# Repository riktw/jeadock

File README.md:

# jeadock
Dock for the Lichee RV to provide Ethernet, GPIO and more

More information on the related [blog post](https://justanotherelectronicsblog.com/?p=1107).

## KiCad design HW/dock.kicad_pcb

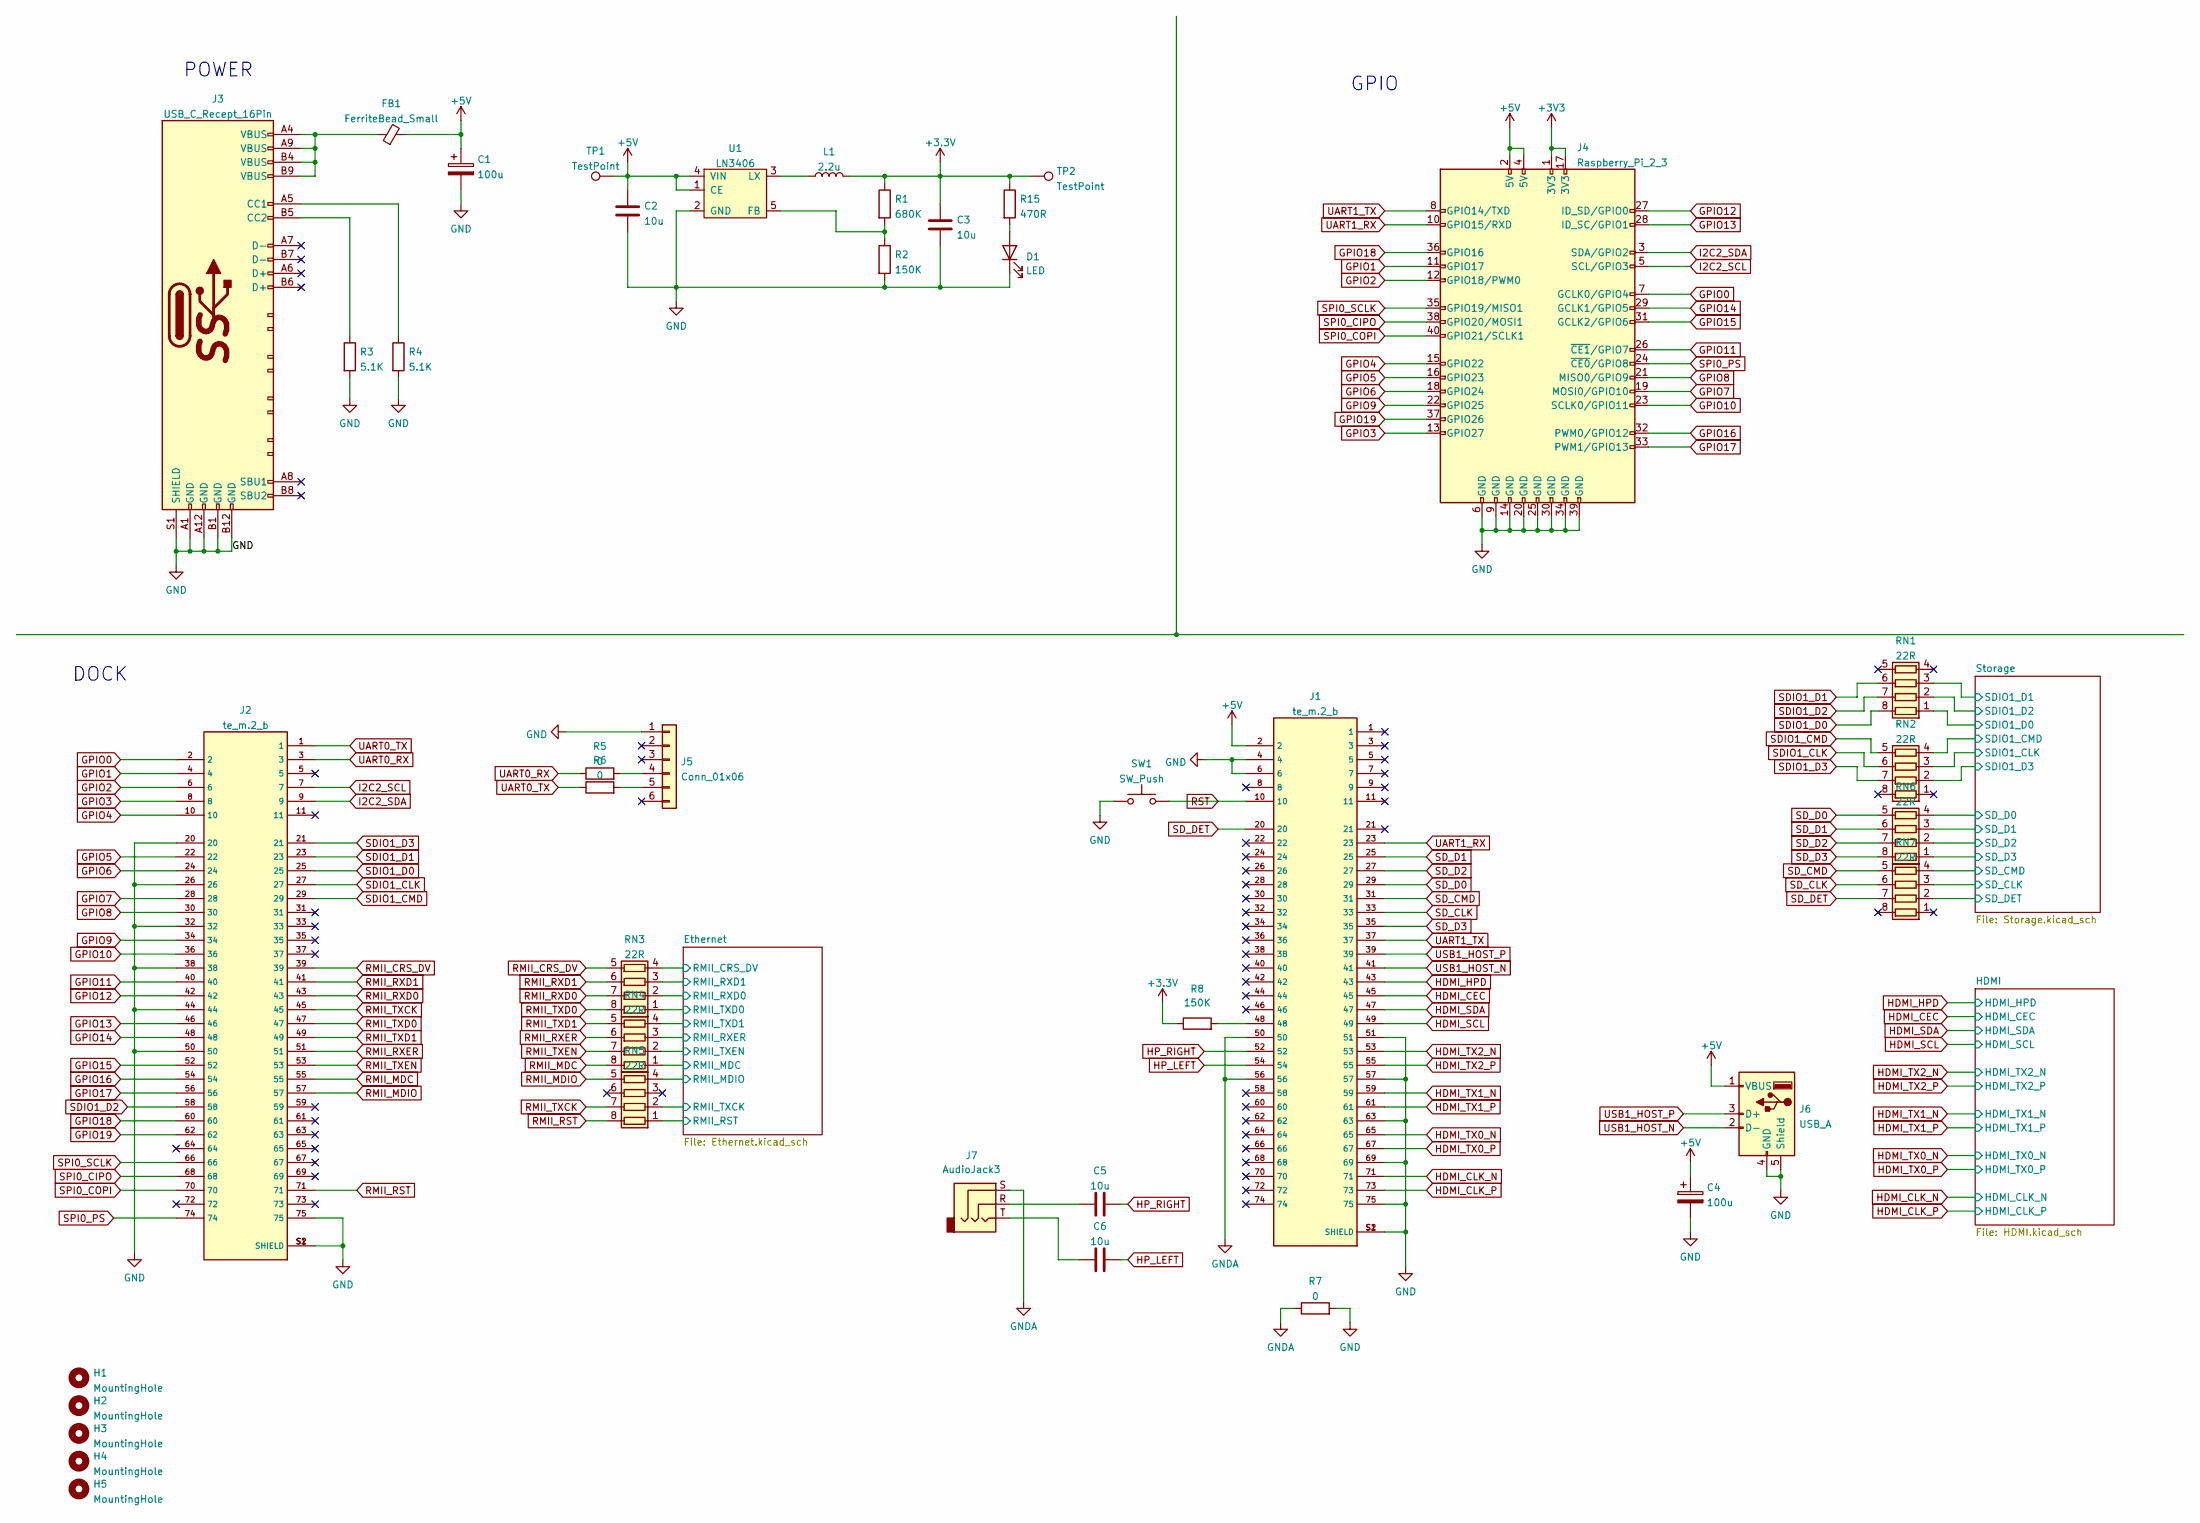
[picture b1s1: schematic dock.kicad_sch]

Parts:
C1, C4: 100u; CP_Elec_6.3x7.7
C2, C3, C5, C6: 10u; C_0603_1608Metric; JLC C96446
D1: LED; LED_0603_1608Metric; JLC C72043
FB1: FerriteBead_Small; L_0603_1608Metric
H1: MountingHole; MountingHole_2.2mm_M2
H2, H3, H4, H5: MountingHole; MountingHole_3.2mm_M3
J1, J2: te_m.2_b; TE_2199230-3; JLC C2761526
J3: USB_C_Recept_16Pin
J4: Raspberry_Pi_2_3; PinHeader_2x20_P2.54mm_Vertical
J5: Conn_01x06; PinHeader_1x06_P2.54mm_Vertical
J6: USB_A; USB_A_CONNFLY_DS1095-WNR0
J7: AudioJack3; audio_jack_3.5_C18167; JLC C18167
L1: 2.2u; L_0805_2012Metric_Pad1.15x1.40mm_HandSolder; Farnell 2776807
R1: 680K; R_0603_1608Metric; JLC C25822
R2, R8: 150K; R_0603_1608Metric; JLC C22807
R3, R4: 5.1K; R_0603_1608Metric; JLC C23186
R5, R6, R7: 0; R_0603_1608Metric
R15: 470R; R_0603_1608Metric
RN1, RN2, RN3, RN4, RN5, RN6, RN7: 22R; R_Array_Convex_4x0402; Farnell 3550014
SW1: SW_Push; SW_SPST_CK_RS282G05A3
TP1, TP2: TestPoint; TestPoint_Pad_1.5x1.5mm
U1: LN3406; SOT-23-5; JLC C190828

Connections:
+5V: C1.1, C2.1, C4.1, FB1.2, J1.2, J4.2 (5V), J4.4 (5V), J6.1 (VBUS), TP1.1, U1.1 (CE), U1.4 (VIN); also elsewhere on the board
/Ethernet/RMII_CRS_DV: RN3.4 (R4.1); also elsewhere on the board
/Ethernet/RMII_MDC: RN4.1 (R1.1); also elsewhere on the board
/Ethernet/RMII_MDIO: RN5.4 (R4.1); also elsewhere on the board
/Ethernet/RMII_RXD0: RN3.2 (R2.1); also elsewhere on the board
/Ethernet/RMII_RXD1: RN3.3 (R3.1); also elsewhere on the board
/Ethernet/RMII_RXER: RN4.3 (R3.1); also elsewhere on the board
/Ethernet/RMII_TXCK: RN5.2 (R2.1); also elsewhere on the board
/Ethernet/RMII_TXD0: RN3.1 (R1.1); also elsewhere on the board
/Ethernet/RMII_TXD1: RN4.4 (R4.1); also elsewhere on the board
/Ethernet/RMII_TXEN: RN4.2 (R2.1); also elsewhere on the board
/Storage/SDIO1_CLK: RN2.3 (R3.1); also elsewhere on the board
/Storage/SDIO1_CMD: RN2.4 (R4.1); also elsewhere on the board
/Storage/SDIO1_D0: RN1.1 (R1.1); also elsewhere on the board
/Storage/SDIO1_D1: RN1.3 (R3.1); also elsewhere on the board
/Storage/SDIO1_D2: RN1.2 (R2.1); also elsewhere on the board
/Storage/SDIO1_D3: RN2.2 (R2.1); also elsewhere on the board
/Storage/SD_CLK: RN7.3 (R3.1); also elsewhere on the board
/Storage/SD_CMD: RN7.4 (R4.1); also elsewhere on the board
/Storage/SD_D0: RN6.4 (R4.1); also elsewhere on the board
/Storage/SD_D1: RN6.3 (R3.1); also elsewhere on the board
/Storage/SD_D2: RN6.2 (R2.1); also elsewhere on the board
/Storage/SD_D3: RN6.1 (R1.1); also elsewhere on the board
/Storage/SD_DET: RN7.2 (R2.1); also elsewhere on the board
GND: C1.2, C2.2, C3.2, C4.2, D1.1 (K), J1.4, J1.6, J1.51, J1.57, J1.63, J1.69, J1.75, J1.S1 (SHIELD), J1.S2 (SHIELD), J2.20, J2.26, J2.32, J2.38, J2.44, J2.50, J2.75, J2.S1 (SHIELD), J2.S2 (SHIELD), J3.A1 (GND), J3.A12 (GND), J3.B1 (GND), J3.B12 (GND), J3.S1 (SHIELD), J4.6 (GND), J4.9 (GND), J4.14 (GND), J4.20 (GND), J4.25 (GND), J4.30 (GND), J4.34 (GND), J4.39 (GND), J5.1, J6.4 (GND), J6.5 (Shield), R2.2, R3.2, R4.2, R7.2, SW1.1, U1.2 (GND); also elsewhere on the board
GNDA: J1.50, J1.56, J7.S, R7.1
GPIO0: J2.2, J4.7 (GCLK0/GPIO4)
GPIO1: J2.4, J4.11 (GPIO17)
GPIO2: J2.6, J4.12 (GPIO18/PWM0)
GPIO3: J2.8, J4.13 (GPIO27)
GPIO4: J2.10, J4.15 (GPIO22)
GPIO5: J2.22, J4.16 (GPIO23)
GPIO6: J2.24, J4.18 (GPIO24)
GPIO7: J2.28, J4.19 (MOSI0/GPIO10)
GPIO8: J2.30, J4.21 (MISO0/GPIO9)
GPIO9: J2.34, J4.22 (GPIO25)
GPIO10: J2.36, J4.23 (SCLK0/GPIO11)
GPIO11: J2.40, J4.26 (~CE1/GPIO7)
GPIO12: J2.42, J4.27 (ID_SD/GPIO0)
GPIO13: J2.46, J4.28 (ID_SC/GPIO1)
GPIO14: J2.48, J4.29 (GCLK1/GPIO5)
GPIO15: J2.52, J4.31 (GCLK2/GPIO6)
GPIO16: J2.54, J4.32 (PWM0/GPIO12)
GPIO17: J2.56, J4.33 (PWM1/GPIO13)
GPIO18: J2.60, J4.36 (GPIO16)
GPIO19: J2.62, J4.37 (GPIO26)
HDMI_CEC: J1.45; also elsewhere on the board
HDMI_CLK_N: J1.71; also elsewhere on the board
HDMI_CLK_P: J1.73; also elsewhere on the board
HDMI_HPD: J1.43; also elsewhere on the board
HDMI_SCL: J1.49; also elsewhere on the board
HDMI_SDA: J1.47; also elsewhere on the board
HDMI_TX0_N: J1.65; also elsewhere on the board
HDMI_TX0_P: J1.67; also elsewhere on the board
HDMI_TX1_N: J1.59; also elsewhere on the board
HDMI_TX1_P: J1.61; also elsewhere on the board
HDMI_TX2_N: J1.53; also elsewhere on the board
HDMI_TX2_P: J1.55; also elsewhere on the board
HP_LEFT: C6.2, J1.54
HP_RIGHT: C5.2, J1.52
I2C2_SCL: J2.7, J4.5 (SCL/GPIO3)
I2C2_SDA: J2.9, J4.3 (SDA/GPIO2)
unnamed: C5.1, J7.R
unnamed: C6.1, J7.T
unnamed: D1.2 (A), R15.2
unnamed: FB1.1, J3.A4 (VBUS), J3.A9 (VBUS), J3.B4 (VBUS), J3.B9 (VBUS)
unnamed: J1.48, R8.2
unnamed: J3.A5 (CC1), R4.1
unnamed: J3.B5 (CC2), R3.1
unnamed: J5.4, R5.2
unnamed: J5.5, R6.2
unnamed: L1.1, U1.3 (LX)
unnamed: R1.2, R2.1, U1.5 (FB)
RMII_CRS_DV: J2.39, RN3.5 (R4.2)
RMII_MDC: J2.55, RN4.8 (R1.2)
RMII_MDIO: J2.57, RN5.5 (R4.2)
RMII_RST: J2.71, RN5.8 (R1.2)
RMII_RXD0: J2.43, RN3.7 (R2.2)
RMII_RXD1: J2.41, RN3.6 (R3.2)
RMII_RXER: J2.51, RN4.6 (R3.2)
RMII_TXCK: J2.45, RN5.7 (R2.2)
RMII_TXD0: J2.47, RN3.8 (R1.2)
RMII_TXD1: J2.49, RN4.5 (R4.2)
RMII_TXEN: J2.53, RN4.7 (R2.2)
RST: J1.10, SW1.2
RST_PHY: RN5.1 (R1.1); also elsewhere on the board
SDIO1_CLK: J2.27, RN2.6 (R3.2)
SDIO1_CMD: J2.29, RN2.5 (R4.2)
SDIO1_D0: J2.25, RN1.8 (R1.2)
SDIO1_D1: J2.23, RN1.6 (R3.2)
SDIO1_D2: J2.58, RN1.7 (R2.2)
SDIO1_D3: J2.21, RN2.7 (R2.2)
SD_CLK: J1.33, RN7.6 (R3.2)
SD_CMD: J1.31, RN7.5 (R4.2)
SD_D0: J1.29, RN6.5 (R4.2)
SD_D1: J1.25, RN6.6 (R3.2)
SD_D2: J1.27, RN6.7 (R2.2)
SD_D3: J1.35, RN6.8 (R1.2)
SD_DET: J1.20, RN7.7 (R2.2)
SPI0_CIPO: J2.68, J4.38 (GPIO20/MOSI1)
SPI0_COPI: J2.70, J4.40 (GPIO21/SCLK1)
SPI0_PS: J2.74, J4.24 (~CE0/GPIO8)
SPI0_SCLK: J2.66, J4.35 (GPIO19/MISO1)
UART0_RX: J2.3, R5.1
UART0_TX: J2.1, R6.1
UART1_RX: J1.23, J4.10 (GPIO15/RXD)
UART1_TX: J1.37, J4.8 (GPIO14/TXD)
USB1_HOST_N: J1.41, J6.2 (D-)
USB1_HOST_P: J1.39, J6.3 (D+)

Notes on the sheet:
GPIO
POWER
DOCK

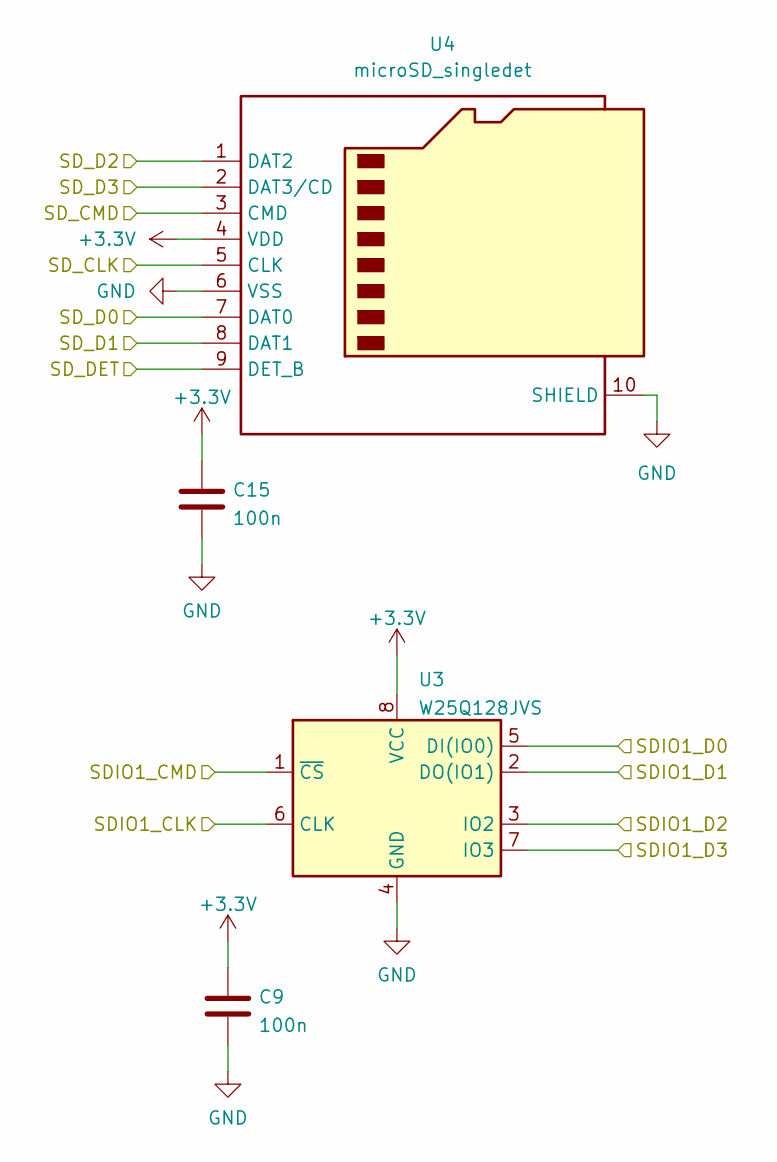
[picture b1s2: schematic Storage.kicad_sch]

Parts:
C9, C15: 100n; C_0603_1608Metric; JLC C14663
U3: W25Q128JVS; SOIC-8_5.23x5.23mm_P1.27mm; JLC C97521
U4: microSD_singledet; microSD Hanbo Electronic TF-018; JLC C961679

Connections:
/Storage/SDIO1_CLK: U3.6 (CLK); also elsewhere on the board
/Storage/SDIO1_CMD: U3.1 (~CS); also elsewhere on the board
/Storage/SDIO1_D0: U3.5 (DI(IO0)); also elsewhere on the board
/Storage/SDIO1_D1: U3.2 (DO(IO1)); also elsewhere on the board
/Storage/SDIO1_D2: U3.3 (IO2); also elsewhere on the board
/Storage/SDIO1_D3: U3.7 (IO3); also elsewhere on the board
/Storage/SD_CLK: U4.5 (CLK); also elsewhere on the board
/Storage/SD_CMD: U4.3 (CMD); also elsewhere on the board
/Storage/SD_D0: U4.7 (DAT0); also elsewhere on the board
/Storage/SD_D1: U4.8 (DAT1); also elsewhere on the board
/Storage/SD_D2: U4.1 (DAT2); also elsewhere on the board
/Storage/SD_D3: U4.2 (DAT3/CD); also elsewhere on the board
/Storage/SD_DET: U4.9 (DET_B); also elsewhere on the board
GND: C9.2, C15.2, U3.4 (GND), U4.6 (VSS), U4.10 (SHIELD); also elsewhere on the board

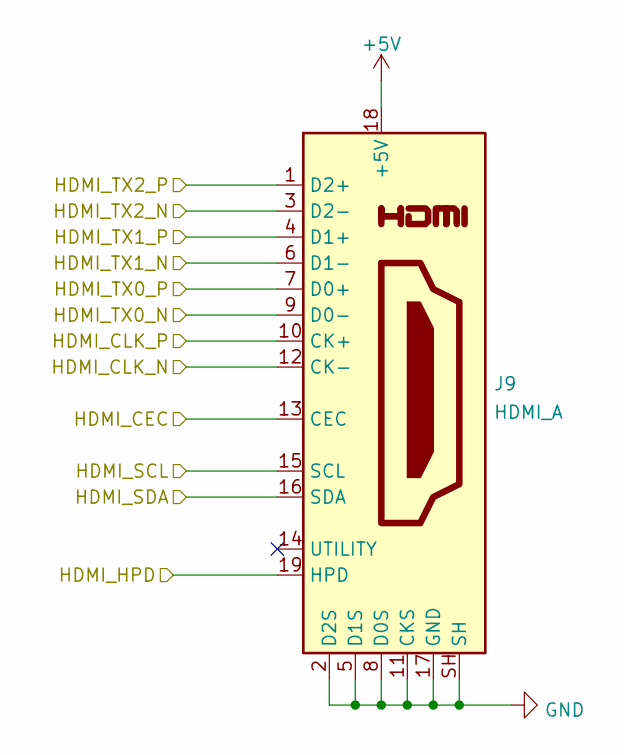
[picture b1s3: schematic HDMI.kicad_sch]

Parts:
J9: HDMI_A; HDMI_A_XUNPU_HDMI-001S; JLC C720616

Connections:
+5V: J9.18 (+5V); also elsewhere on the board
GND: J9.2 (D2S), J9.5 (D1S), J9.8 (D0S), J9.11 (CKS), J9.17 (GND), J9.SH; also elsewhere on the board
HDMI_CEC: J9.13 (CEC); also elsewhere on the board
HDMI_CLK_N: J9.12 (CK-); also elsewhere on the board
HDMI_CLK_P: J9.10 (CK+); also elsewhere on the board
HDMI_HPD: J9.19 (HPD); also elsewhere on the board
HDMI_SCL: J9.15 (SCL); also elsewhere on the board
HDMI_SDA: J9.16 (SDA); also elsewhere on the board
HDMI_TX0_N: J9.9 (D0-); also elsewhere on the board
HDMI_TX0_P: J9.7 (D0+); also elsewhere on the board
HDMI_TX1_N: J9.6 (D1-); also elsewhere on the board
HDMI_TX1_P: J9.4 (D1+); also elsewhere on the board
HDMI_TX2_N: J9.3 (D2-); also elsewhere on the board
HDMI_TX2_P: J9.1 (D2+); also elsewhere on the board

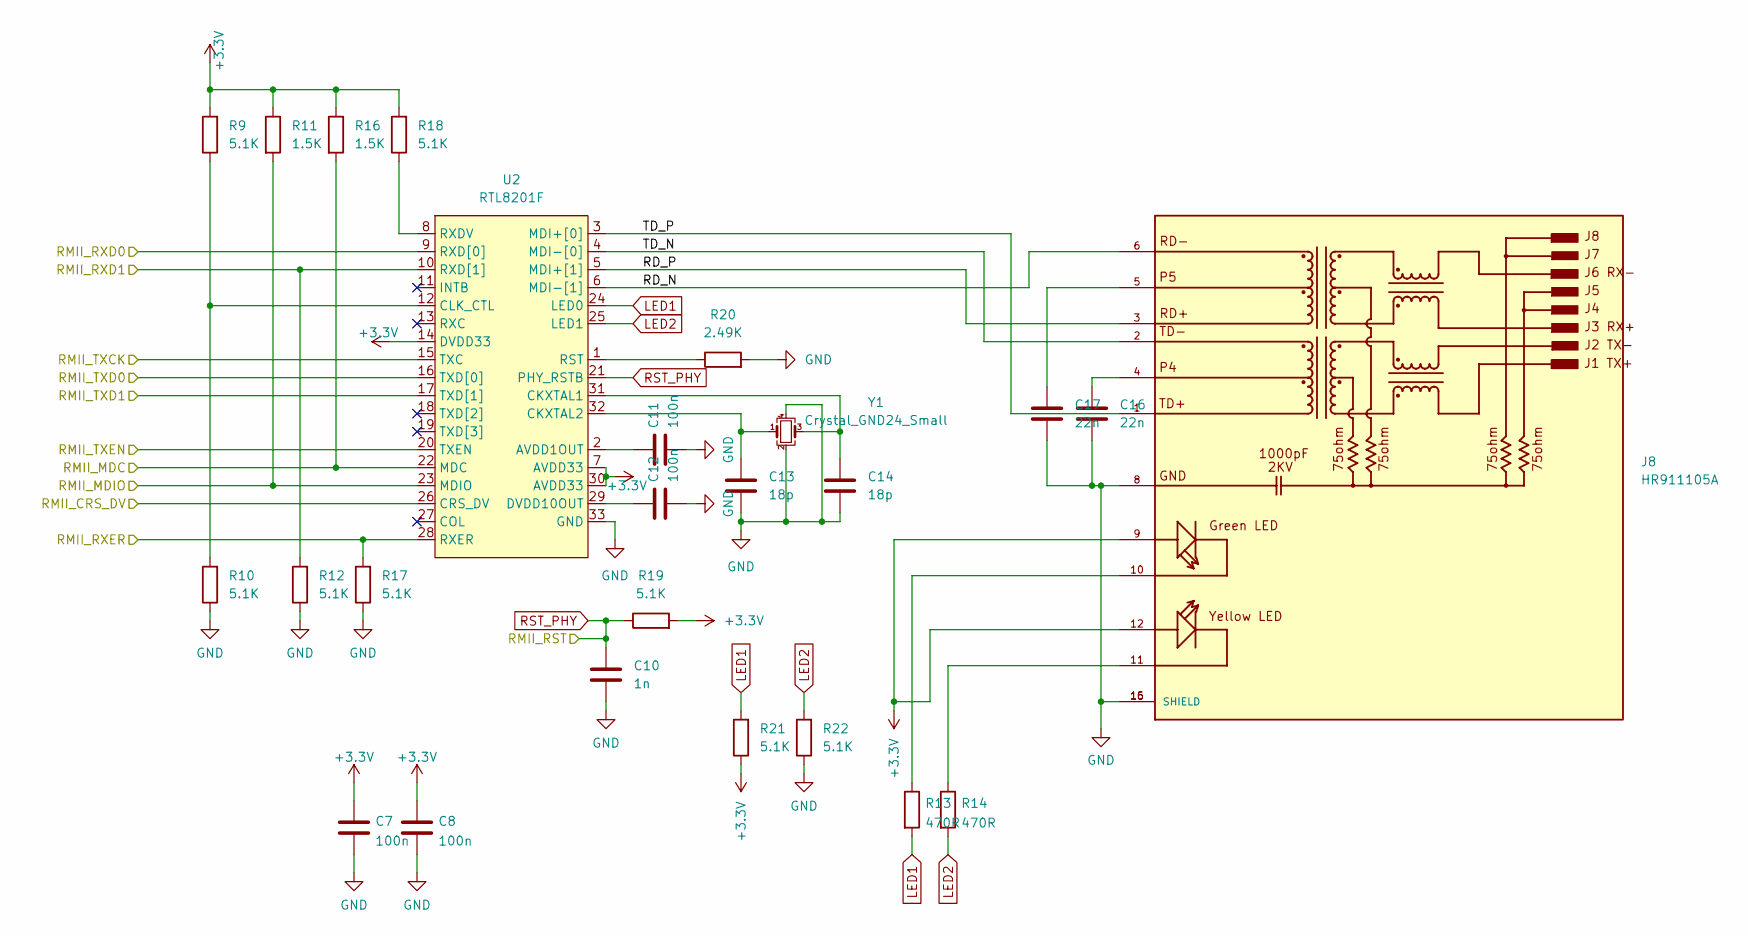
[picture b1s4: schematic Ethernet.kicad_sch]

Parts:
C7, C8, C11, C12: 100n; C_0402_1005Metric; JLC C307331
C10: 1n; C_0402_1005Metric; JLC C1523
C13, C14: 18p; C_0603_1608Metric; JLC C1647
C16, C17: 22n; C_0603_1608Metric; JLC C1647
J8: HR911105A; HANRUN_HR911105A; PARTREV A; JLC C12074
R9, R10: 5.1K; R_0603_1608Metric
R11, R16: 1.5K; R_0603_1608Metric; JLC C22843
R12, R17, R18, R19, R21, R22: 5.1K; R_0603_1608Metric; JLC C23186
R13, R14: 470R; R_0603_1608Metric
R20: 2.49K; R_0603_1608Metric
U2: RTL8201F; QFN-32-1EP_5x5mm_P0.5mm_EP3.3x3.3mm; JLC C45044
Y1: Crystal_GND24_Small; Crystal_SMD_3225-4Pin_3.2x2.5mm; JLC C90913

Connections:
/Ethernet/RD_N: J8.6, U2.6 (MDI-[1]); also elsewhere on the board
/Ethernet/RD_P: J8.3, U2.5 (MDI+[1]); also elsewhere on the board
/Ethernet/RMII_CRS_DV: U2.26 (CRS_DV); also elsewhere on the board
/Ethernet/RMII_MDC: R16.2, U2.22 (MDC); also elsewhere on the board
/Ethernet/RMII_MDIO: R11.2, U2.23 (MDIO); also elsewhere on the board
/Ethernet/RMII_RXD0: U2.9 (RXD[0]); also elsewhere on the board
/Ethernet/RMII_RXD1: R12.2, U2.10 (RXD[1]); also elsewhere on the board
/Ethernet/RMII_RXER: R17.2, U2.28 (RXER); also elsewhere on the board
/Ethernet/RMII_TXCK: U2.15 (TXC); also elsewhere on the board
/Ethernet/RMII_TXD0: U2.16 (TXD[0]); also elsewhere on the board
/Ethernet/RMII_TXD1: U2.17 (TXD[1]); also elsewhere on the board
/Ethernet/RMII_TXEN: U2.20 (TXEN); also elsewhere on the board
/Ethernet/TD_N: J8.2, U2.4 (MDI-[0]); also elsewhere on the board
/Ethernet/TD_P: J8.1, U2.3 (MDI+[0]); also elsewhere on the board
GND: C7.2, C8.2, C10.2, C11.2, C12.2, C13.2, C14.2, C16.2, C17.2, J8.8, J8.15 (SHIELD), J8.16 (SHIELD), R10.1, R12.1, R17.1, R20.2, R22.1, U2.33 (GND), Y1.2, Y1.4; also elsewhere on the board
LED1: R13.2, R21.2, U2.24 (LED0)
LED2: R14.2, R22.2, U2.25 (LED1)
unnamed: C11.1, U2.2 (AVDD1OUT)
unnamed: C12.1, U2.29 (DVDD10OUT)
unnamed: C13.1, U2.32 (CKXTAL2), Y1.1
unnamed: C14.1, U2.31 (CKXTAL1), Y1.3
unnamed: C16.1, J8.4
unnamed: C17.1, J8.5
unnamed: J8.10, R13.1
unnamed: J8.11, R14.1
unnamed: R9.1, R10.2, U2.12 (CLK_CTL)
unnamed: R18.1, U2.8 (RXDV)
unnamed: R20.1, U2.1 (RST)
RST_PHY: C10.1, R19.1, U2.21 (PHY_RSTB); also elsewhere on the board

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
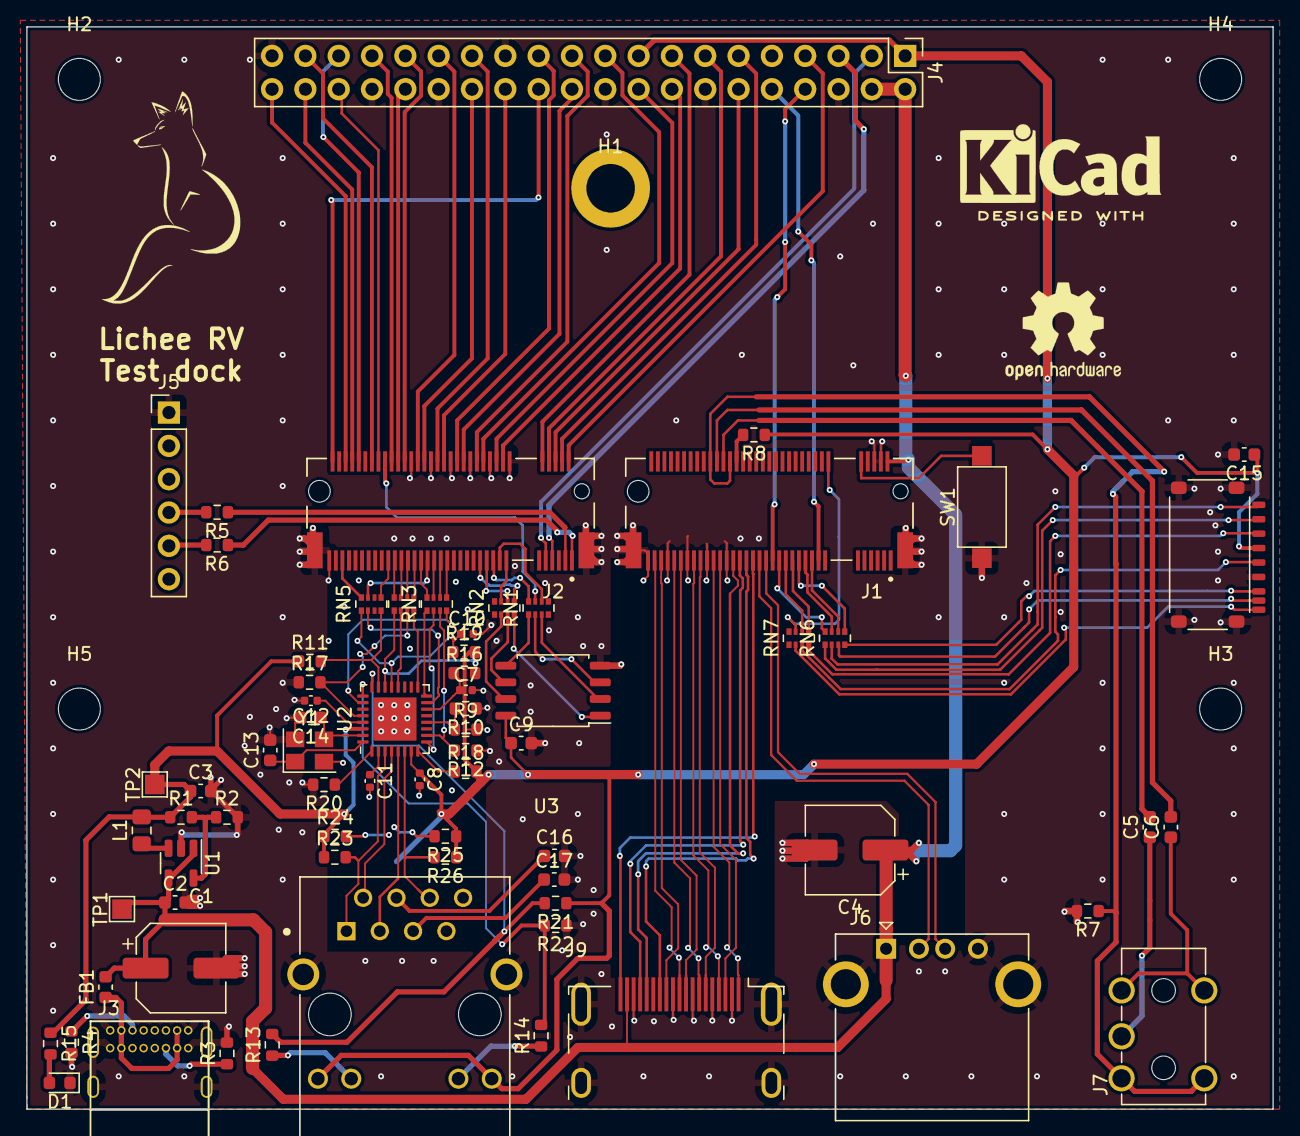
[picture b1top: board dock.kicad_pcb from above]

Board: 4 copper layers, 95.0 x 82.5 mm, 75 parts (0 on the bottom side), 127 nets.

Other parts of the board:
R23, R24, R25, R26: 49.9R; R_0603_1608Metric

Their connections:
/Ethernet/RD_N: R26.2; also elsewhere on the board
/Ethernet/RD_P: R25.2; also elsewhere on the board
/Ethernet/TD_N: R24.2; also elsewhere on the board
/Ethernet/TD_P: R23.2; also elsewhere on the board

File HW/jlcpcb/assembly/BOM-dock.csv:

Comment,Designator,Footprint,LCSC
LN3406,U1,SOT-23-5, C190828 
HR911105A,J8,HANRUN_HR911105A,C12074
100n,"C15,C9",C_0603_1608Metric,C14663
1n,C10,C_0402_1005Metric,C1523
18p,"C13,C14,C16",C_0603_1608Metric,C1647
AudioJack3,J7,audio_jack_3.5_C18167,C18167
150K,"R2,R8",R_0603_1608Metric,C22807
1.5K,"R11,R16",R_0603_1608Metric,C22843
5.1K,"R12,R17,R18,R19,R21,R22,R3,R4",R_0603_1608Metric,C23186
22R,"RN1,RN2,RN3,RN4,RN5,RN6,RN7",R_Array_Convex_4x0402,C25499
680K,R1,R_0603_1608Metric,C25822
te_m.2_b,"J1,J2",TE_2199230-3,C2761526
100n,"C11,C12,C7,C8",C_0402_1005Metric,C307331
RTL8201F,U2,QFN-32-1EP_5x5mm_P0.5mm_EP3.3x3.3mm,C45044
LED,D1,LED_0603_1608Metric,C72043
HDMI_A,J9,HDMI_A_XUNPU_HDMI-001S,C720616
Crystal_GND24_Small,Y1,Crystal_SMD_3225-4Pin_3.2x2.5mm,C90913
microSD_singledet,U4,microSD Hanbo Electronic TF-018,C961679
10u,"C2,C3,C5,C6",C_0603_1608Metric,C96446
W25Q128JVS,U3,SOIC-8_5.23x5.23mm_P1.27mm,C97521
470R,R15,R_0603_1608Metric,
TestPoint,TP1,TestPoint_Pad_1.5x1.5mm,
MountingHole,H4,MountingHole_3.2mm_M3,
MountingHole,H5,MountingHole_3.2mm_M3,
MountingHole,H1,MountingHole_2.2mm_M2,
MountingHole,H2,MountingHole_3.2mm_M3,
TestPoint,TP2,TestPoint_Pad_1.5x1.5mm,
MountingHole,H3,MountingHole_3.2mm_M3,

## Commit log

2022-04-24 Added initial hardware
2022-04-24 Added schematic in pdf and pinout
2022-04-30 Added initial SW to create an arch image for the dock, added case files
2022-05-02 Small fixes to HW
2022-05-05 Added link to blog to readme
